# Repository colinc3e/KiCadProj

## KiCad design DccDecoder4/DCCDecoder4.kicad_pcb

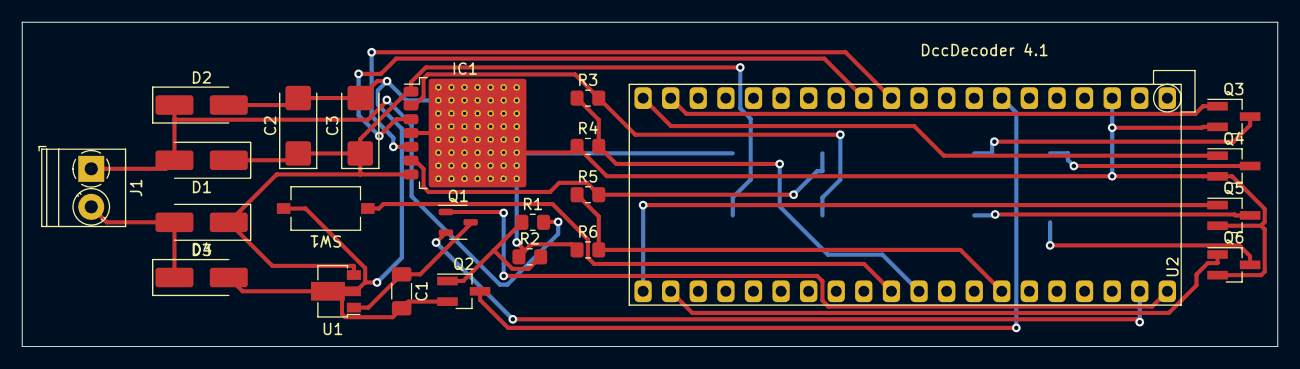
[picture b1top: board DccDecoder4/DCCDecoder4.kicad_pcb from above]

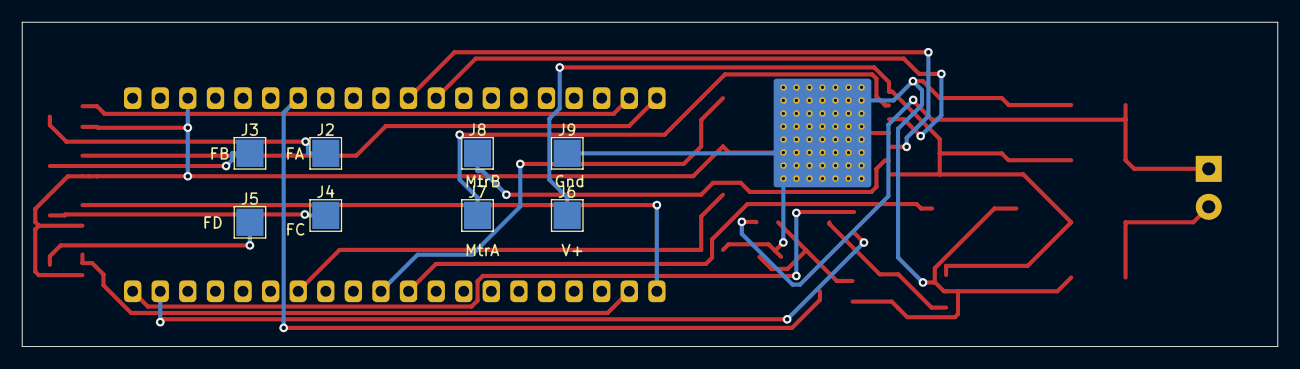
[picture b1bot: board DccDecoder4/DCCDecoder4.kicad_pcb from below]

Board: 2 copper layers, 115.6 x 29.8 mm, 32 parts (8 on the bottom side), 24 nets.

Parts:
C1: 10uf/16V; C_1206_3216Metric_Pad1.33x1.80mm_HandSolder
C2: 10uF/25V; CP_EIA-6032-20_AVX-F_Pad2.25x2.35mm_HandSolder
C3: 10uF/25v; CP_EIA-6032-20_AVX-F_Pad2.25x2.35mm_HandSolder
D1, D2, D3, D4: RBR3L60AD; D_SMA_Handsoldering
IC1: BD62321HFP-TR; Rohm_HRP7
J1: Screw_Terminal_01x02; TerminalBlock_Phoenix_PT-1,5-2-3.5-H_1x02_P3.50mm_Horizontal
J2: 0; TestPoint_Pad_2.5x2.5mm
J3: 1; TestPoint_Pad_2.5x2.5mm
J4: 2; TestPoint_Pad_2.5x2.5mm
J5: 3; TestPoint_Pad_2.5x2.5mm
J6: +V; TestPoint_Pad_2.5x2.5mm
J7: M_OUT_B; TestPoint_Pad_2.5x2.5mm
J8: M_OUT_A; TestPoint_Pad_2.5x2.5mm
J9: GND; TestPoint_Pad_2.5x2.5mm
Q1: DMG2305UX-7; SOT-23-3
Q2, Q3, Q4, Q5, Q6: 2N7002BK; SOT-23_Handsoldering
R1, R2, R3, R5: 6k8; R_0805_2012Metric_Pad1.20x1.40mm_HandSolder
R4, R6: 1k; R_0805_2012Metric_Pad1.20x1.40mm_HandSolder
SW1: SW_Push; SW_Tactile_SPST_NO_Straight_CK_PTS636Sx25SMTRLFS
U1: AP7384-50Y; SOT-89-3
U2: Pico_RaspberryPico; RaspberryPico_TH_NoSWD

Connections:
+V: C2.1, C3.1, D1.1 (K), D4.1 (K), IC1.1 (VCC_1), IC1.7 (VCC_2), J6.1, U1.3 (VI)
/+3V3: C1.1, Q1.3, U1.1 (VO)
/ADC_EMF_A: R3.1, R4.2, U2.31 (GPIO26)
/MOTOR_OUT_A: IC1.2 (OUT1), J7.1, R3.2
/MOTOR_OUT_B: IC1.6 (OUT2), J8.1, R5.2
/VSYS: Q1.2, U2.39 (VSYS)
ADC_EMF_B: R5.1, R6.2, U2.34 (GPIO28)
DCC_IN: Q2.3 (D), U2.7 (GPIO5)
FUNC_A: Q3.1 (G), U2.19 (GPIO14)
FUNC_B: Q4.1 (G), U2.20 (GPIO15)
FUNC_C: Q5.1 (G), U2.21 (GPIO16)
FUNC_D: Q6.1 (G), U2.22 (GPIO17)
GND: C1.2, C2.2, C3.2, D2.2 (A), D3.2 (A), IC1.4 (GND_1), J9.1, Q2.2 (S), Q3.2 (S), Q4.2 (S), Q5.2 (S), Q6.2 (S), R2.1, R4.1, R6.1, SW1.2, U1.2 (GND), U2.3 (GND)
unnamed: D1.2 (A), D2.1 (K), J1.1, R1.2
unnamed: D3.1 (K), D4.2 (A), J1.2
unnamed: J2.1, Q3.3 (D)
unnamed: J3.1, Q4.3 (D)
unnamed: J4.1, Q5.3 (D)
unnamed: J5.1, Q6.3 (D)
unnamed: Q2.1 (G), R1.1, R2.2
unnamed: SW1.1, U2.30 (RUN)
unnamed: Q1.1, U2.40 (VBUS)
PWM_F: IC1.3 (FIN), U2.12 (GPIO9)
PWM_R: IC1.5 (RIN), U2.11 (GPIO8)

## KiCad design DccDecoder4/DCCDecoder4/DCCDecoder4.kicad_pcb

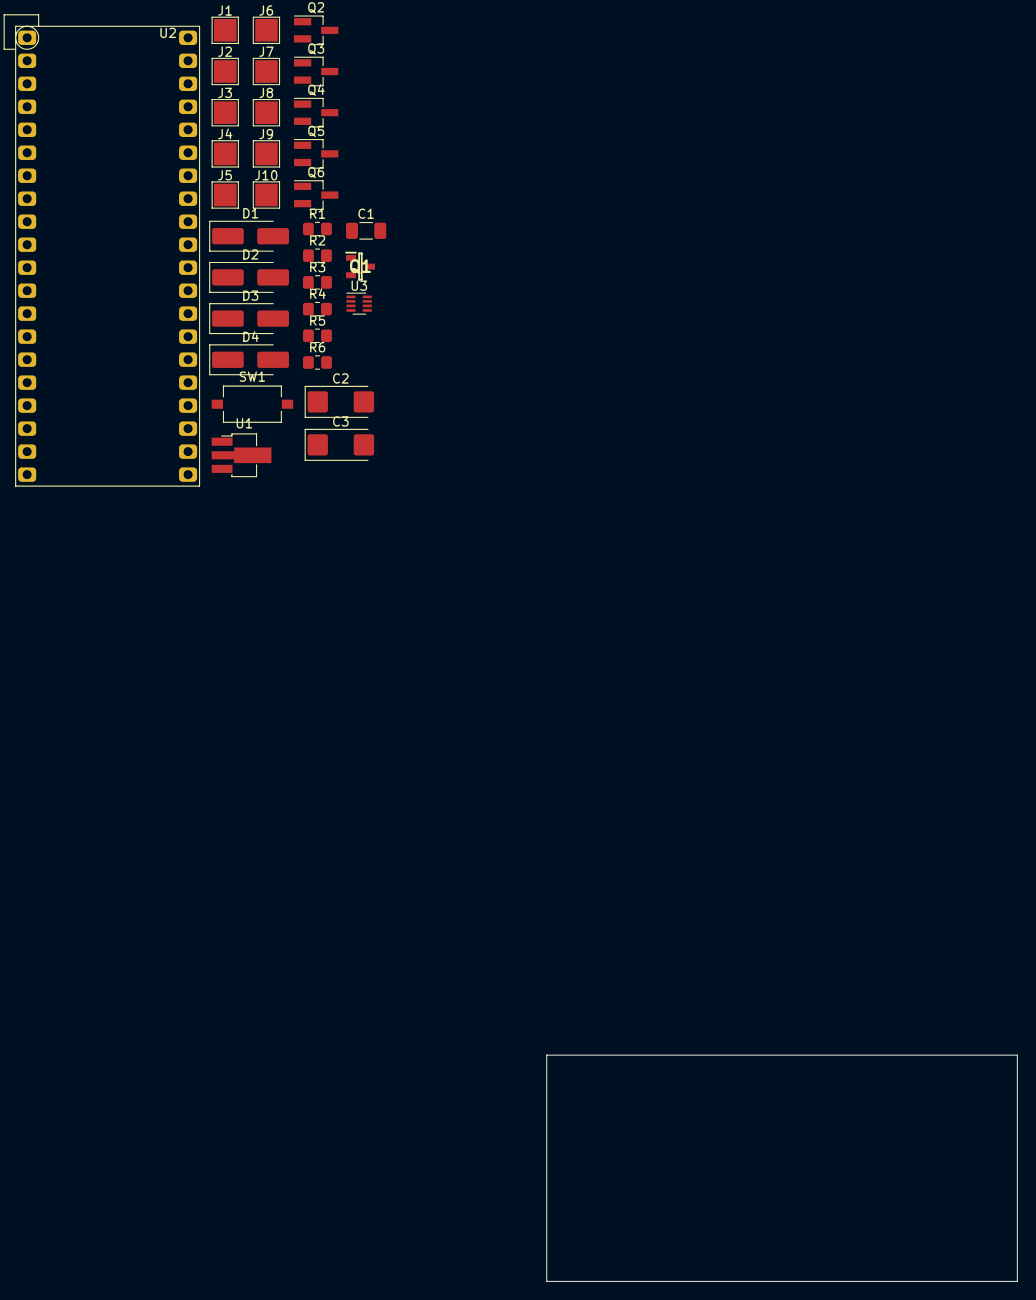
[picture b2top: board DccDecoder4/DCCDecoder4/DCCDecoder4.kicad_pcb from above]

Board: 2 copper layers, 52.0 x 25.0 mm, 33 parts (0 on the bottom side), 24 nets, no tracks yet.

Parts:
C1: 10uf/16V; C_1206_3216Metric_Pad1.33x1.80mm_HandSolder
C2: 10uF/25V; CP_EIA-6032-20_AVX-F_Pad2.25x2.35mm_HandSolder
C3: 10uF/25v; CP_EIA-6032-20_AVX-F_Pad2.25x2.35mm_HandSolder
D1, D2, D3, D4: RBR3L60AD; D_SMA_Handsoldering
J1, J2: PAD; TestPoint_Pad_2.5x2.5mm
J3: 0; TestPoint_Pad_2.5x2.5mm
J4: 1; TestPoint_Pad_2.5x2.5mm
J5: 2; TestPoint_Pad_2.5x2.5mm
J6: 3; TestPoint_Pad_2.5x2.5mm
J7: +V; TestPoint_Pad_2.5x2.5mm
J8: M_OUT_B; TestPoint_Pad_2.5x2.5mm
J9: M_OUT_A; TestPoint_Pad_2.5x2.5mm
J10: GND; TestPoint_Pad_2.5x2.5mm
Q1: DMG2305UX-7; SOT96P240X110-3N
Q2, Q3, Q4, Q5, Q6: 2N7002K; SOT-23_Handsoldering
R1, R2, R3, R5: 6k8; R_0805_2012Metric_Pad1.20x1.40mm_HandSolder
R4, R6: 1k; R_0805_2012Metric_Pad1.20x1.40mm_HandSolder
SW1: SW_Push; SW_Tactile_SPST_NO_Straight_CK_PTS636Sx25SMTRLFS
U1: AP7384-33Y; SOT-89-3_Handsoldering
U2: Pico_RaspberryPico; RaspberryPico_TH_NoSWD
U3: BDR6133; SC-70-8

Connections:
+3V3: C1.1, Q1.3, U1.1 (VO), U3.2 (VCC)
+V: C2.1, C3.1, D1.1 (K), D4.1 (K), J7.1, U1.3 (VI), U3.3 (VM)
/ADC_EMF_A: R3.1, R4.2, U2.31 (GPIO26)
/ADC_EMF_B: R5.1, R6.2, U2.32 (GPIO27)
/GPIO14: U2.19 (GPIO14), U3.6 (INA)
/GPIO15: U2.20 (GPIO15), U3.7 (INB)
/GPIO16: Q3.1 (G), U2.21 (GPIO16)
/GPIO17: Q4.1 (G), U2.22 (GPIO17)
/GPIO18: Q5.1 (G), U2.24 (GPIO18)
/GPIO19: Q6.1 (G), U2.25 (GPIO19)
/GPIO21: Q2.3 (D), U2.27 (GPIO21)
/MOTOR_OUT_A: J8.1, R3.2, U3.4 (OUTA)
/MOTOR_OUT_B: J9.1, R5.2, U3.5 (OUTB)
/VSYS: Q1.2, U2.39 (VSYS)
GND: C1.2, C2.2, C3.2, D2.2 (A), D3.2 (A), J10.1, Q2.2 (S), Q3.2 (S), Q4.2 (S), Q5.2 (S), Q6.2 (S), R2.1, R4.1, R6.1, SW1.2, U1.2 (GND), U2.3 (GND), U3.1 (GND)
unnamed: D1.2 (A), D2.1 (K), J1.1, R1.2
unnamed: D3.1 (K), D4.2 (A), J2.1
unnamed: J3.1, Q3.3 (D)
unnamed: J4.1, Q4.3 (D)
unnamed: J5.1, Q5.3 (D)
unnamed: J6.1, Q6.3 (D)
unnamed: Q2.1 (G), R1.1, R2.2
unnamed: SW1.1, U2.30 (RUN)
unnamed: Q1.1, U2.40 (VBUS)

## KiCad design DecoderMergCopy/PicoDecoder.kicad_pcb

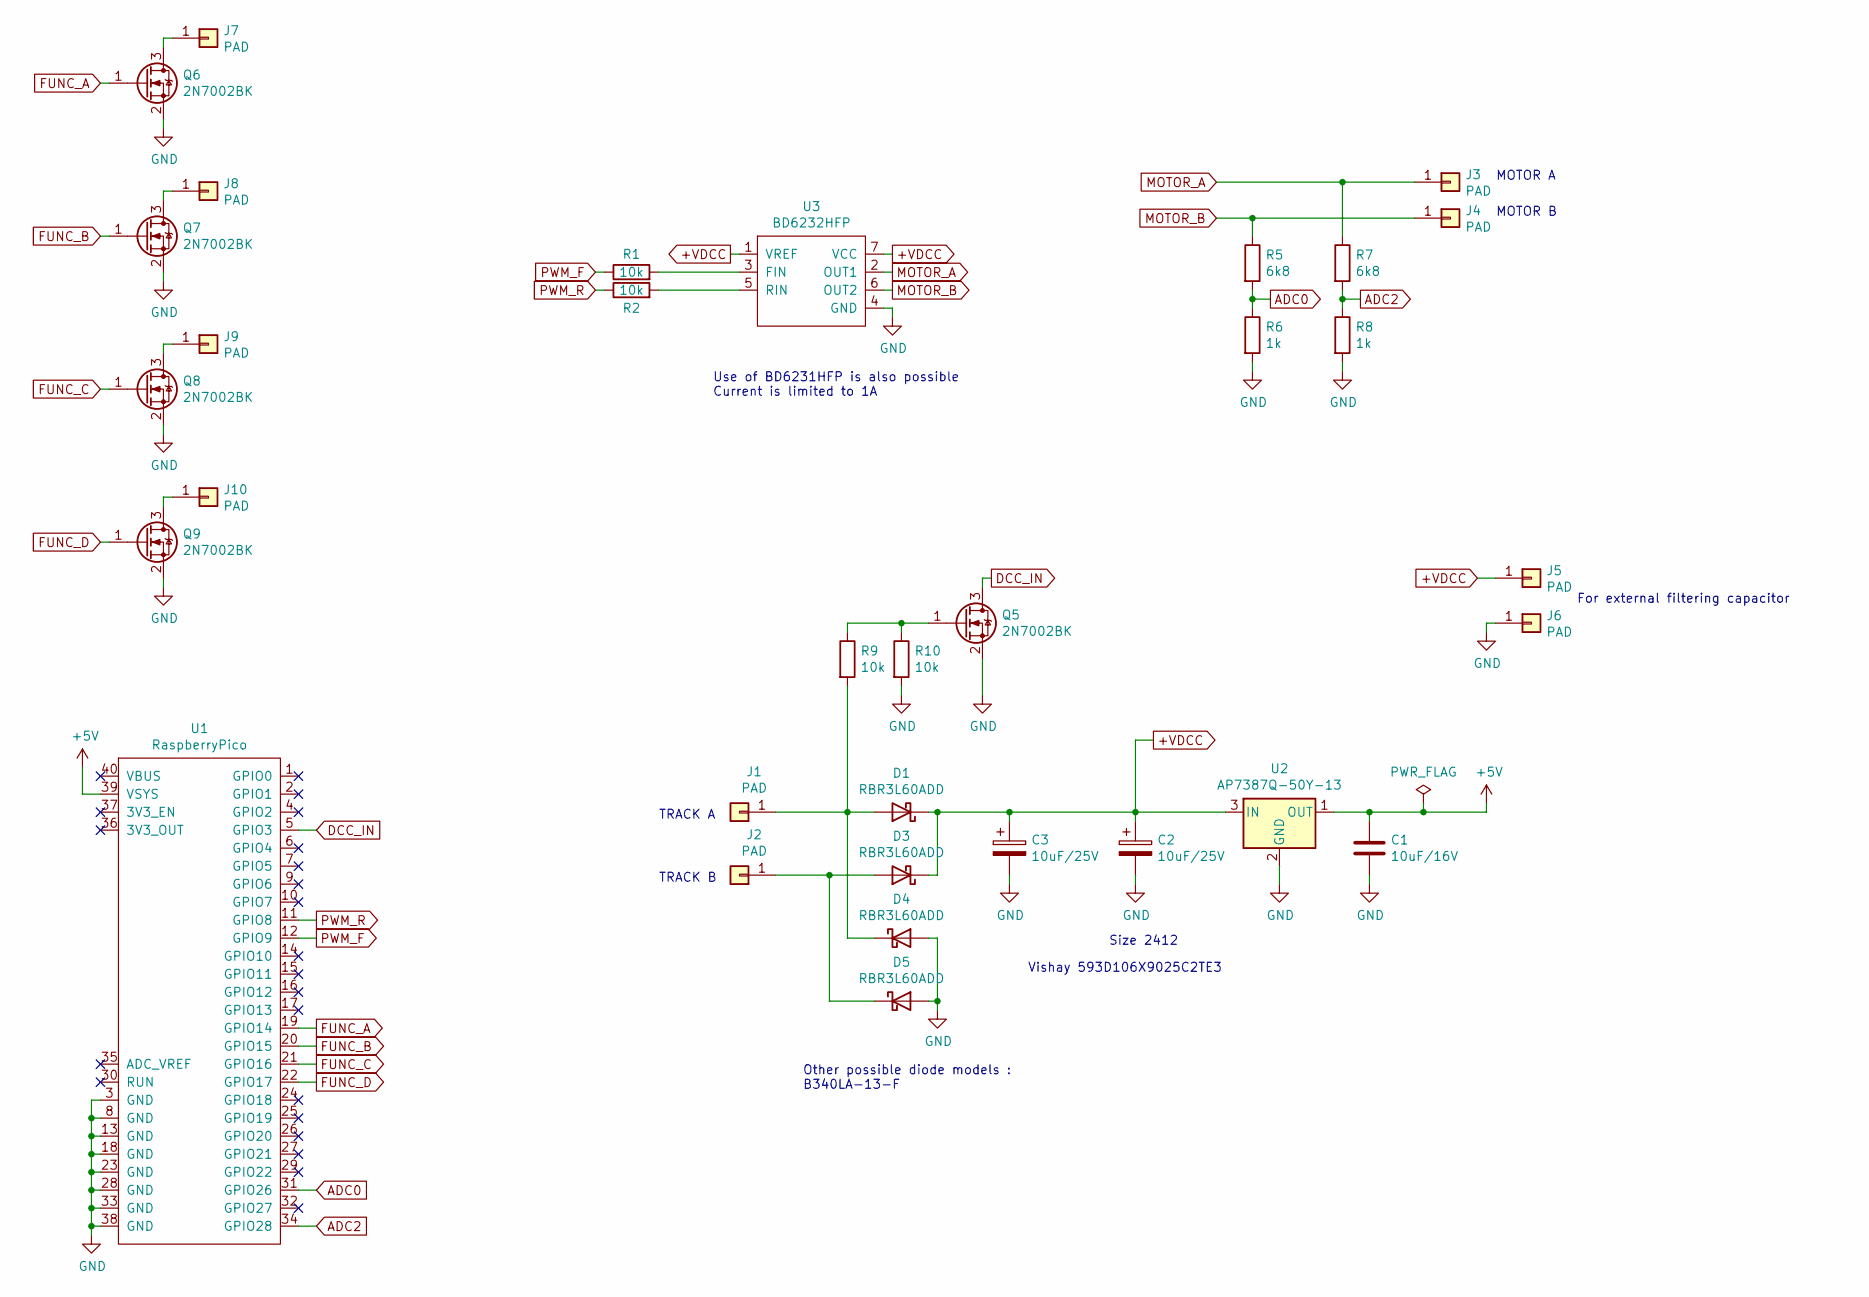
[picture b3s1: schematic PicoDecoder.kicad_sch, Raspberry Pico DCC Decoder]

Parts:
C1: 10uF/16V; C_1206_3216Metric_Pad1.33x1.80mm_HandSolder
C2, C3: 10uF/25V; CP_EIA-6032-20_AVX-F_Pad2.25x2.35mm_HandSolder
D1, D3, D4, D5: RBR3L60ADD; D_SMA_Handsoldering
J1, J2, J3, J4, J5, J6, J7, J8, J9, J10: PAD; TestPoint_Pad_2.5x2.5mm
Q5, Q6, Q7, Q8, Q9: 2N7002BK; SOT-23_Handsoldering
R1, R2, R9, R10: 10k; R_0805_2012Metric_Pad1.20x1.40mm_HandSolder
R5, R7: 6k8; R_0805_2012Metric_Pad1.20x1.40mm_HandSolder
R6, R8: 1k; R_0805_2012Metric_Pad1.20x1.40mm_HandSolder
U1: RaspberryPico; RaspberryPico_TH_NoSWD
U2: AP7387Q-50Y-13; SOT-89-3_Handsoldering
U3: BD6232HFP; Rohm_HRP7

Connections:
+5V: C1.1, U1.39 (VSYS), U2.1 (OUT)
+VDCC: C2.1, C3.1, D1.1 (K), D3.1 (K), J5.1, U2.3 (IN), U3.1 (VREF), U3.7 (VCC)
ADC0: R5.2, R6.1, U1.31 (GPIO26)
ADC2: R7.2, R8.1, U1.34 (GPIO28)
DCC_IN: Q5.3 (D), U1.5 (GPIO3)
FUNC_A: Q6.1 (G), U1.19 (GPIO14)
FUNC_B: Q7.1 (G), U1.20 (GPIO15)
FUNC_C: Q8.1 (G), U1.21 (GPIO16)
FUNC_D: Q9.1 (G), U1.22 (GPIO17)
GND: C1.2, C2.2, C3.2, D4.2 (A), D5.2 (A), J6.1, Q5.2 (S), Q6.2 (S), Q7.2 (S), Q8.2 (S), Q9.2 (S), R6.2, R8.2, R10.2, U1.3 (GND), U1.8 (GND), U1.13 (GND), U1.18 (GND), U1.23 (GND), U1.28 (GND), U1.33 (GND), U1.38 (GND), U2.2 (GND), U3.4 (GND)
MOTOR_A: J3.1, R7.1, U3.2 (OUT1)
MOTOR_B: J4.1, R5.1, U3.6 (OUT2)
unnamed: D1.2 (A), D4.1 (K), J1.1, R9.2
unnamed: D3.2 (A), D5.1 (K), J2.1
unnamed: J7.1, Q6.3 (D)
unnamed: J8.1, Q7.3 (D)
unnamed: J9.1, Q8.3 (D)
unnamed: J10.1, Q9.3 (D)
unnamed: Q5.1 (G), R9.1, R10.1
unnamed: R1.2, U3.3 (FIN)
unnamed: R2.2, U3.5 (RIN)
PWM_F: R1.1, U1.12 (GPIO9)
PWM_R: R2.1, U1.11 (GPIO8)

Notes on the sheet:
MOTOR A
Other possible diode models : B340LA-13-F
Size 2412
MOTOR B
TRACK B
Vishay 593D106X9025C2TE3
For external filtering capacitor
TRACK A
Use of BD6231HFP is also possible Current is limited to 1A

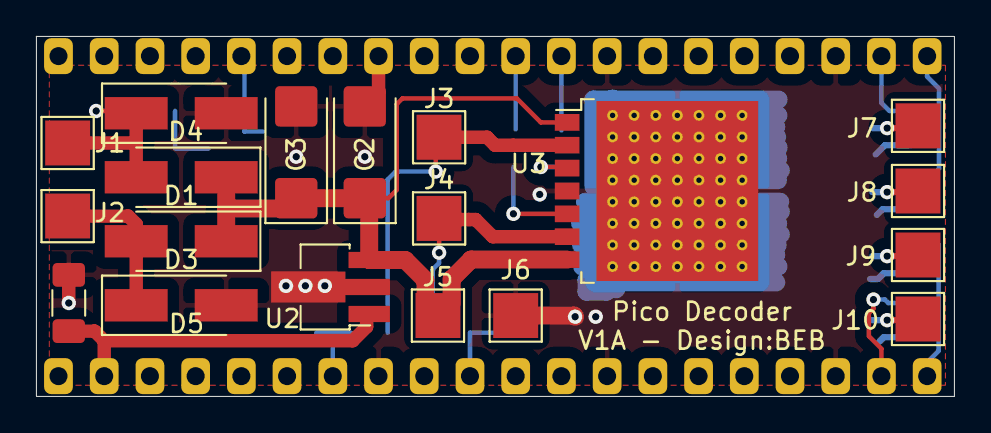
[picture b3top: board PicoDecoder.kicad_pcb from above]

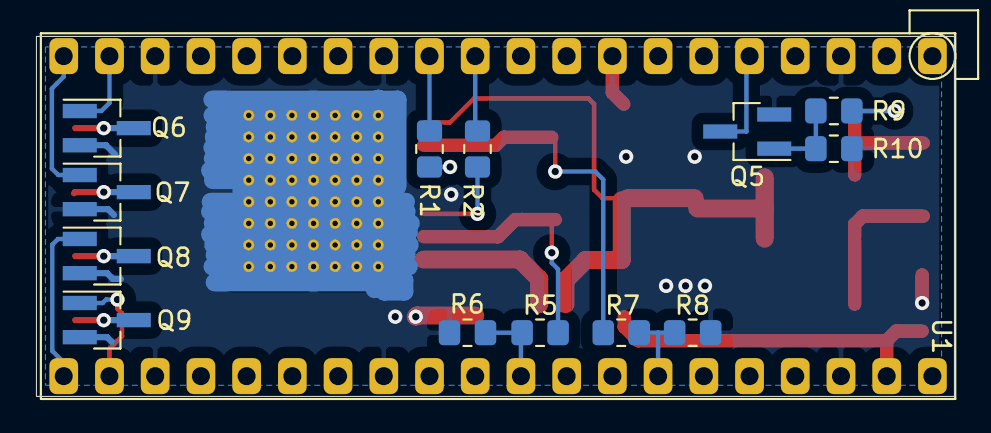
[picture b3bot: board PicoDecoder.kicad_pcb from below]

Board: 2 copper layers, 51.0 x 20.0 mm, 33 parts (14 on the bottom side), 23 nets.

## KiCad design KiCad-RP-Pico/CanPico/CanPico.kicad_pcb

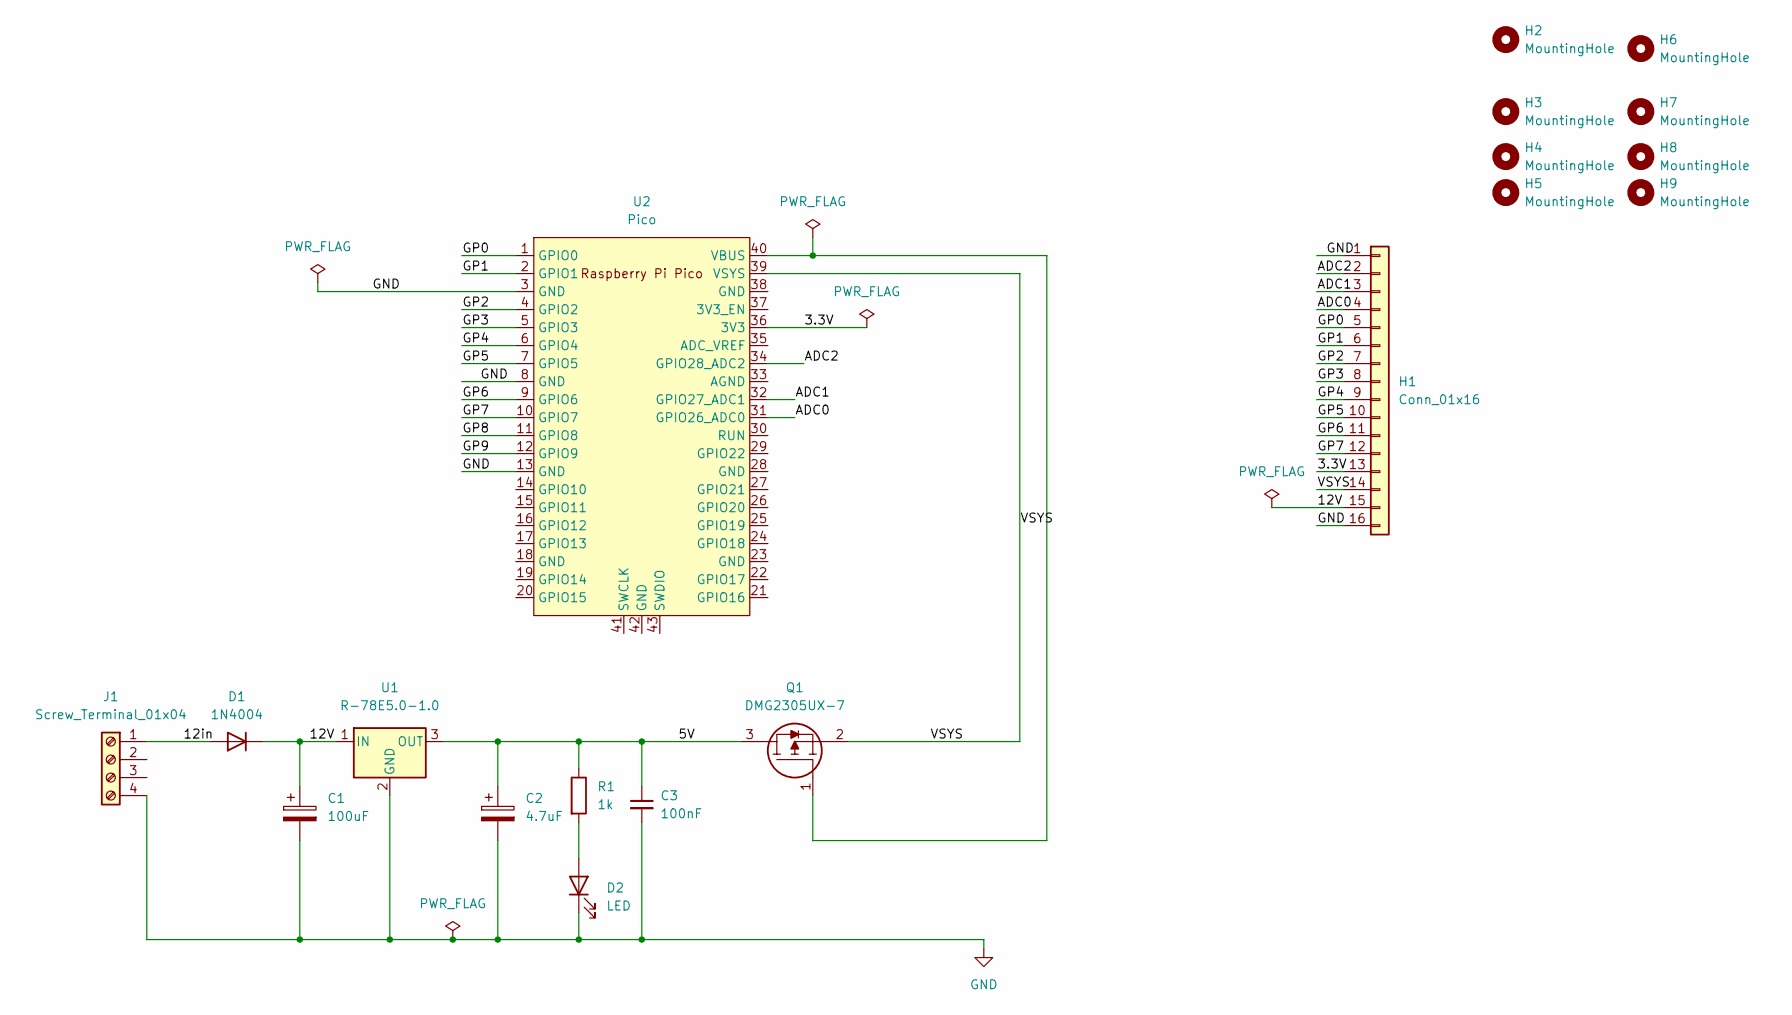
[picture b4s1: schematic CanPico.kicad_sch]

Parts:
C1: 100uF; CP_Radial_D6.3mm_P2.50mm
C2: 4.7uF; CP_Radial_D4.0mm_P1.50mm
C3: 100nF; C_Disc_D5.0mm_W2.5mm_P2.50mm
D1: 1N4004; D_DO-41_SOD81_P10.16mm_Horizontal
D2: LED; LED_D3.0mm
H1: Conn_01x16; PinHeader_1x16_P2.54mm_Vertical
H2, H3, H4, H5, H6, H7, H8, H9: MountingHole; MountingHole_3.2mm_M3
J1: Screw_Terminal_01x04; TerminalBlock_MetzConnect_Type059_RT06304HBWC_1x04_P3.50mm_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
Q1: DMG2305UX-7; SOT-23; Mouser Part Number 621-DMG2305UX-7
R1: 1k; R_Axial_DIN0207_L6.3mm_D2.5mm_P7.62mm_Horizontal
U1: R-78E5.0-1.0; Converter_DCDC_RECOM_R-78E-0.5_THT
U2: Pico; RPi_Pico_SMD_TH

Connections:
/3.3V: H1.13, U2.36 (3V3)
/5V: C2.1, C3.1, Q1.3, R1.1, U1.3 (OUT)
/12V: C1.1, D1.1 (K), H1.15, U1.1 (IN)
/12in: D1.2 (A), J1.1
/ADC0: H1.4, U2.31 (GPIO26_ADC0)
/ADC1: H1.3, U2.32 (GPIO27_ADC1)
/ADC2: H1.2, U2.34 (GPIO28_ADC2)
/GP0: H1.5, U2.1 (GPIO0)
/GP1: H1.6, U2.2 (GPIO1)
/GP2: H1.7, U2.4 (GPIO2)
/GP3: H1.8, U2.5 (GPIO3)
/GP4: H1.9, U2.6 (GPIO4)
/GP5: H1.10, U2.7 (GPIO5)
/GP6: H1.11, U2.9 (GPIO6)
/GP7: H1.12, U2.10 (GPIO7)
/GP8: U2.11 (GPIO8)
/GP9: U2.12 (GPIO9)
/VSYS: H1.14, Q1.2, U2.39 (VSYS)
GND: C1.2, C2.2, C3.2, D2.1 (K), H1.1, H1.16, J1.4, U1.2 (GND), U2.3 (GND), U2.8 (GND), U2.13 (GND)
unnamed: D2.2 (A), R1.2
unnamed: Q1.1, U2.40 (VBUS)

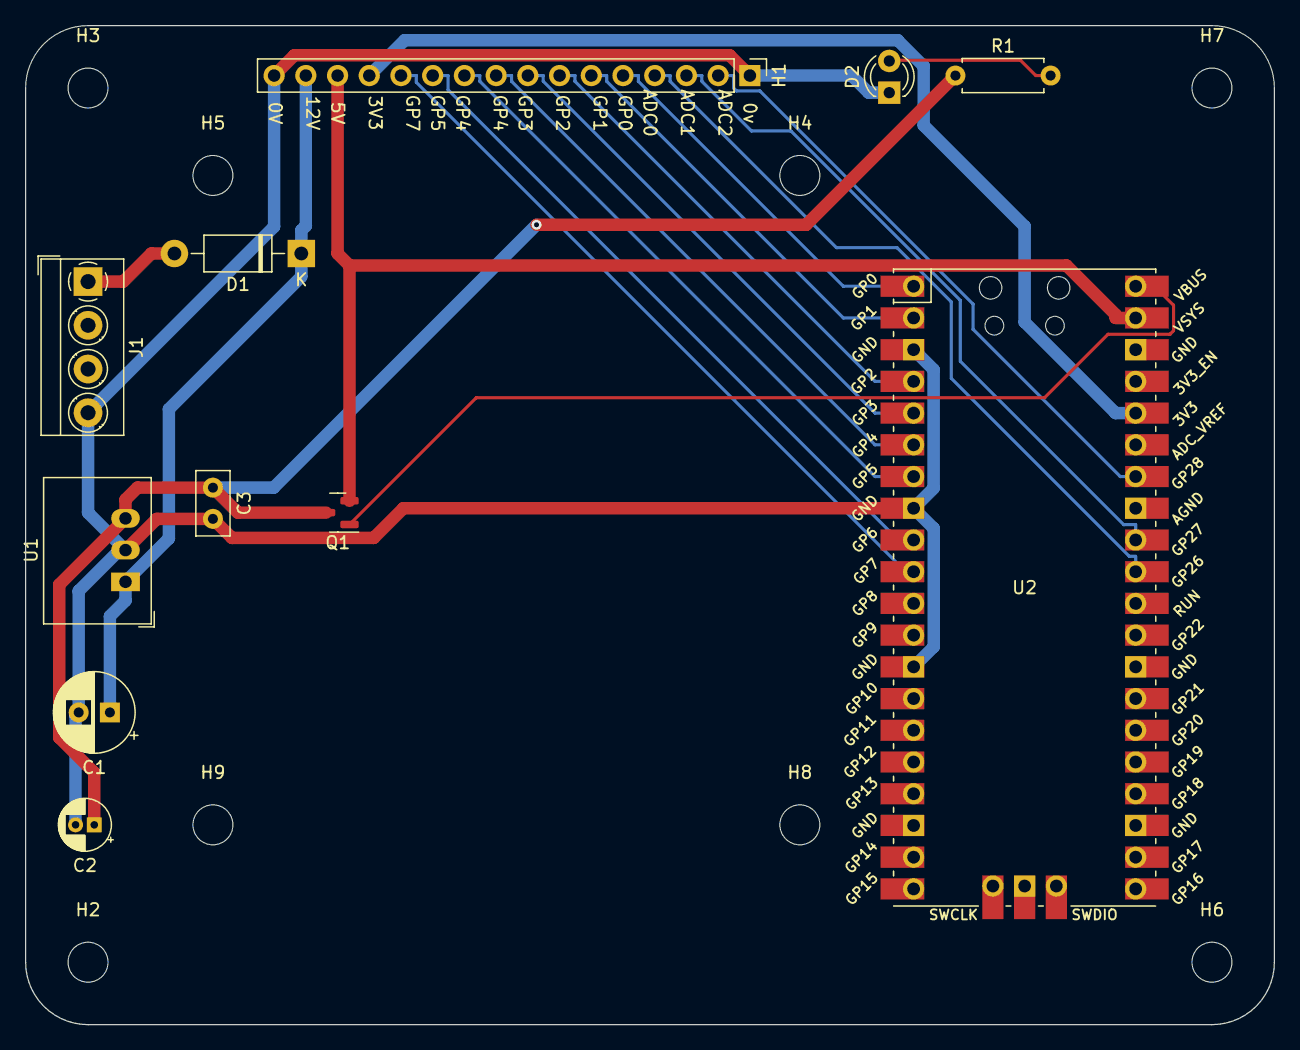
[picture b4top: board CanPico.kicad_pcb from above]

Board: 2 copper layers, 100.0 x 80.0 mm, 19 parts (0 on the bottom side), 19 nets.

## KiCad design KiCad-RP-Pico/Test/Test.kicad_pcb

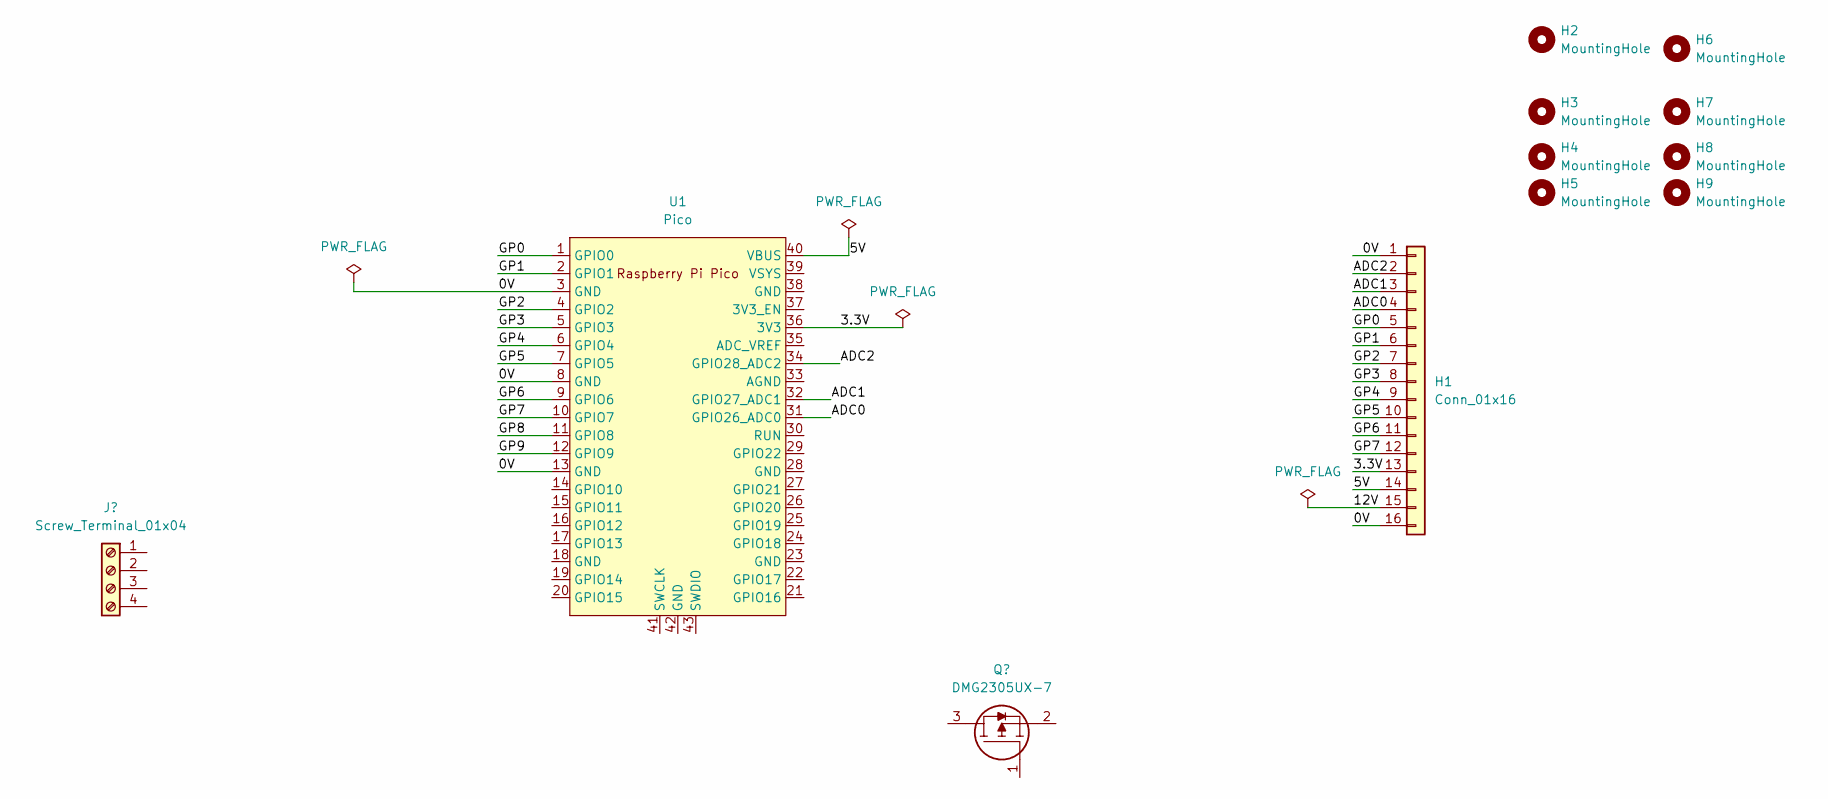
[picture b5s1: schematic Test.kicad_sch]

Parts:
H1: Conn_01x16; PinHeader_1x16_P2.54mm_Vertical
H2, H3, H4, H5, H6, H7, H8, H9: MountingHole; MountingHole_3.2mm_M3
U1: Pico; RPi_Pico_SMD_TH

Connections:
/0V: H1.1, H1.16, U1.3 (GND), U1.8 (GND), U1.13 (GND)
/3.3V: H1.13, U1.36 (3V3)
/5V: H1.14, U1.40 (VBUS)
/12V: H1.15
/ADC0: H1.4, U1.31 (GPIO26_ADC0)
/ADC1: H1.3, U1.32 (GPIO27_ADC1)
/ADC2: H1.2, U1.34 (GPIO28_ADC2)
/GP0: H1.5, U1.1 (GPIO0)
/GP1: H1.6, U1.2 (GPIO1)
/GP2: H1.7, U1.4 (GPIO2)
/GP3: H1.8, U1.5 (GPIO3)
/GP4: H1.9, U1.6 (GPIO4)
/GP5: H1.10, U1.7 (GPIO5)
/GP6: H1.11, U1.9 (GPIO6)
/GP7: H1.12, U1.10 (GPIO7)
/GP8: U1.11 (GPIO8)
/GP9: U1.12 (GPIO9)

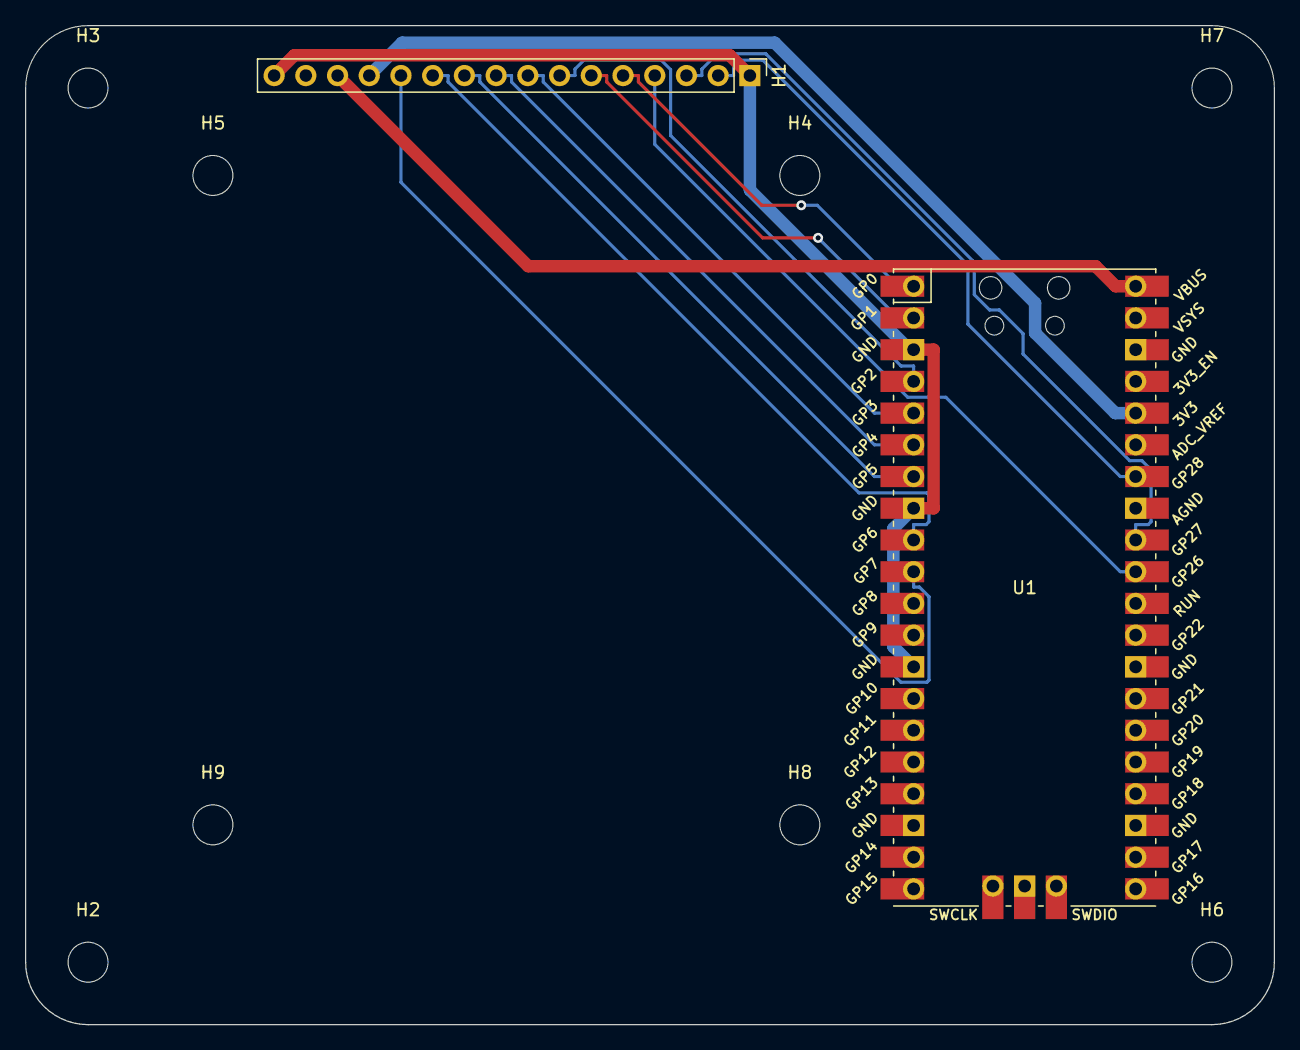
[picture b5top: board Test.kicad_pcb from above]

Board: 2 copper layers, 100.0 x 80.0 mm, 10 parts (0 on the bottom side), 14 nets.

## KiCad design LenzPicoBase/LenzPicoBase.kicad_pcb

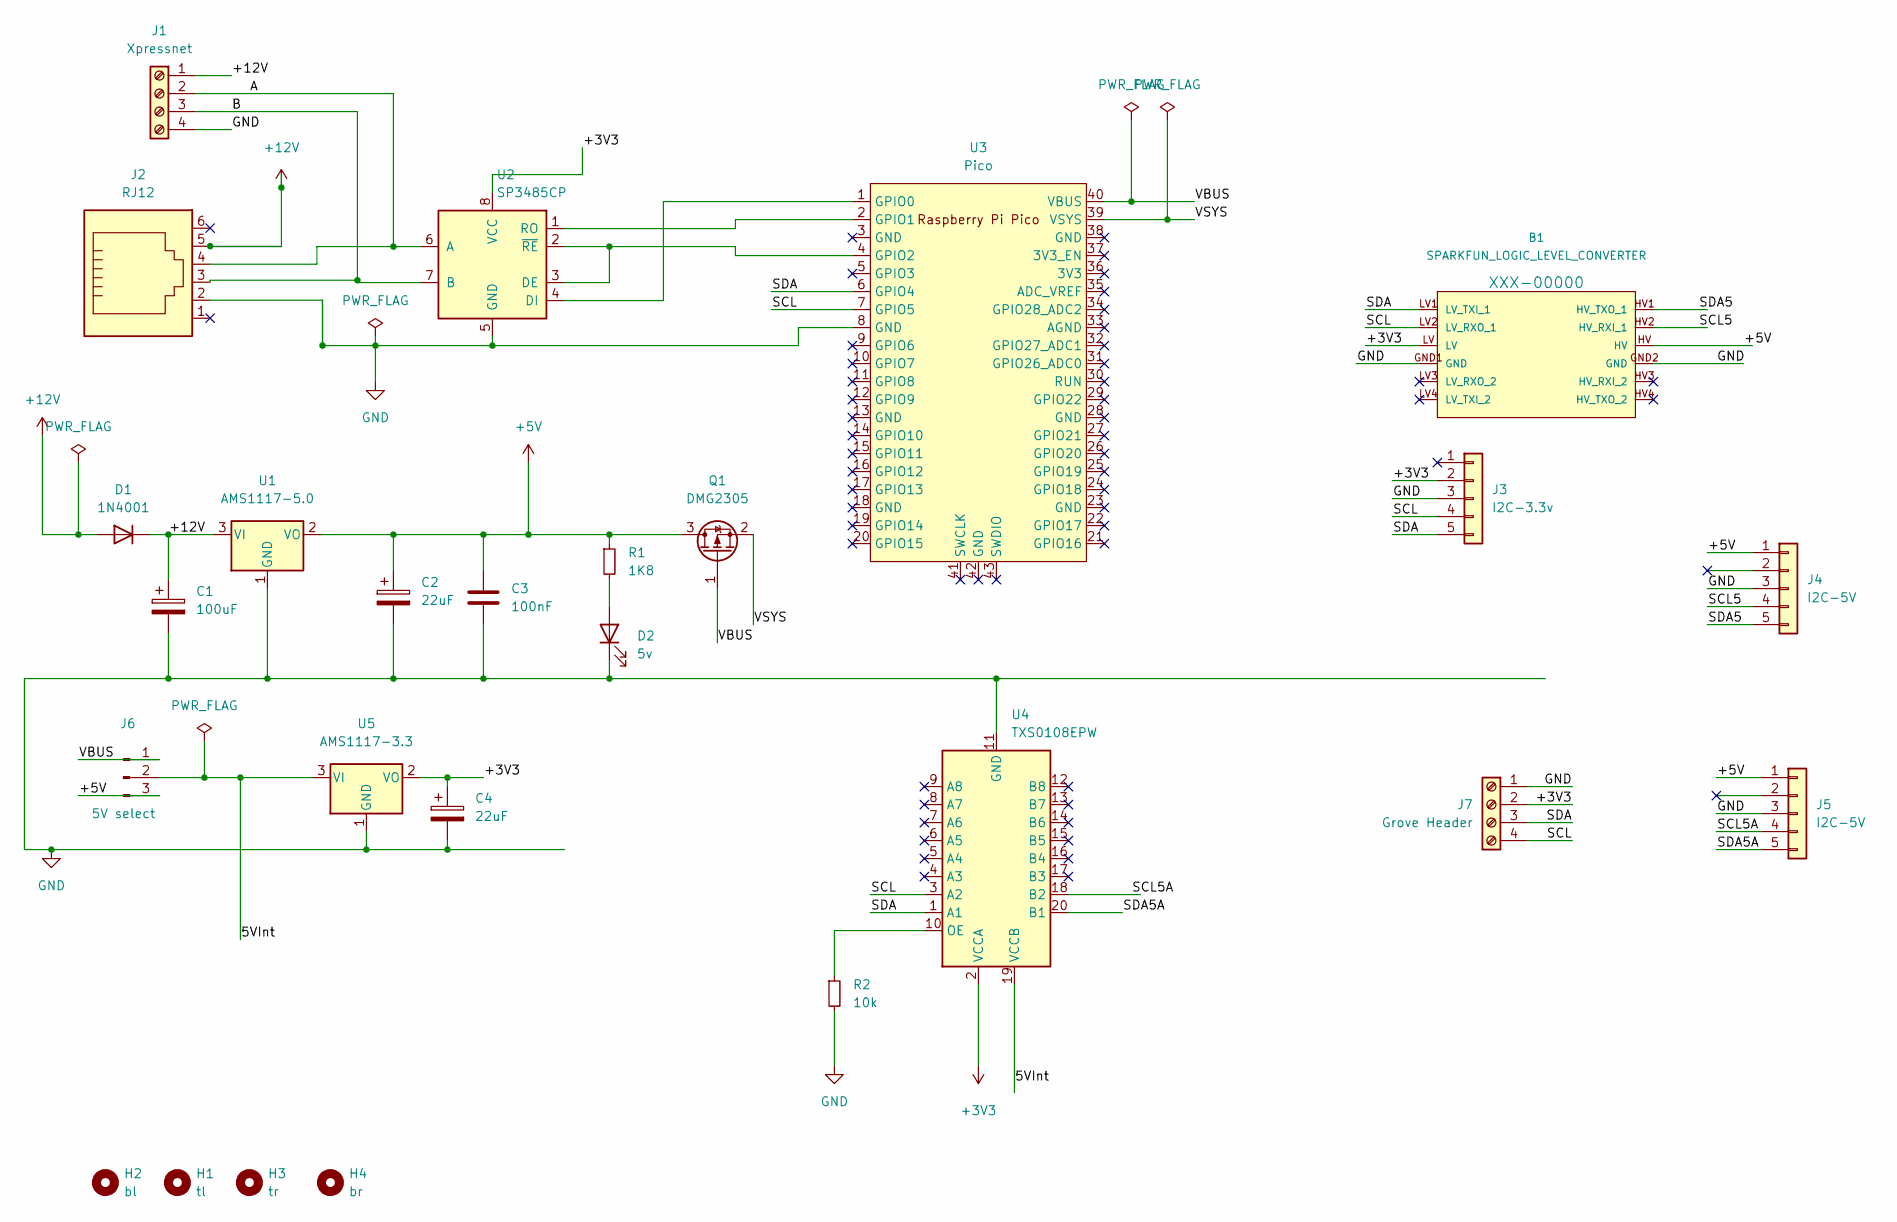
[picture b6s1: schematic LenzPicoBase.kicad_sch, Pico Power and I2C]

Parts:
B1: SPARKFUN_LOGIC_LEVEL_CONVERTER
C1: 100uF; CP_Radial_D8.0mm_P3.80mm
C2, C4: 22uF; CP_Radial_Tantal_D5.0mm_P5.00mm
C3: 100nF; C_Disc_D4.3mm_W1.9mm_P5.00mm
D1: 1N4001; D_DO-35_SOD27_P12.70mm_Horizontal
D2: 5v; LED_D3.0mm
H1: tl; MountingHole_3.2mm_M3_ISO7380
H2: bl; MountingHole_3.2mm_M3_ISO7380
H3: tr; MountingHole_3.2mm_M3_ISO7380
H4: br; MountingHole_3.2mm_M3_ISO7380
J1: Xpressnet; TerminalBlock_Phoenix_PT-1,5-4-3.5-H_1x04_P3.50mm_Horizontal
J2: RJ12; RJ12_Molex
J3: I2C-3.3v; PinHeader_1x05_P2.54mm_Vertical
J4, J5: I2C-5V; PinHeader_1x05_P2.54mm_Vertical
J6: 5V select; PinHeader_1x03_P2.54mm_Vertical
J7: Grove Header; Molex_KK-254_AE-6410-04A_1x04_P2.54mm_Vertical
Q1: DMG2305; SOT-23
R1: 1K8; R_Axial_DIN0207_L6.3mm_D2.5mm_P10.16mm_Horizontal
R2: 10k; R_Axial_DIN0207_L6.3mm_D2.5mm_P10.16mm_Horizontal
U1: AMS1117-5.0; SOT-223-3_TabPin2
U2: SP3485CP; DIP-8_W7.62mm
U3: Pico; RPi_Pico_SMD_TH
U4: TXS0108EPW; TSSOP-20_4.4x6.5mm_P0.65mm
U5: AMS1117-3.3; SOT-223-3_TabPin2

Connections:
+3V3: B1.LV, C4.1, J3.2, J7.2, U2.8 (VCC), U4.2 (VCCA), U5.2 (VO)
+5V: B1.HV, C2.1, C3.1, J4.1, J5.1, J6.3, Q1.3 (D), R1.1, U1.2 (VO)
+12V: C1.1, D1.1 (K), D1.2 (A), J1.1, J2.5, U1.3 (VI)
/5VInt: J6.2, U4.19 (VCCB), U5.3 (VI)
/A: J1.2, J2.4, U2.6 (A)
/B: J1.3, J2.3, U2.7 (B)
/SCL: B1.LV2 (LV_RXO_1), J3.4, J7.4, U3.7 (GPIO5), U4.3 (A2)
/SCL5: B1.HV2 (HV_RXI_1), J4.4
/SCL5A: J5.4, U4.18 (B2)
/SDA: B1.LV1 (LV_TXI_1), J3.5, J7.3, U3.6 (GPIO4), U4.1 (A1)
/SDA5: B1.HV1 (HV_TXO_1), J4.5
/SDA5A: J5.5, U4.20 (B1)
/VBUS: J6.1, Q1.1 (G), U3.40 (VBUS)
/VSYS: Q1.2 (S), U3.39 (VSYS)
GND: B1.GND1 (GND), B1.GND2 (GND), C1.2, C2.2, C3.2, C4.2, D2.1 (K), J1.4, J2.2, J3.3, J4.3, J5.3, J7.1, R2.2, U1.1 (GND), U2.5 (GND), U3.8 (GND), U4.11 (GND), U5.1 (GND)
unnamed: D2.2 (A), R1.2
unnamed: R2.1, U4.10 (OE)
unnamed: U2.1 (RO), U3.2 (GPIO1)
unnamed: U2.2 (~RE), U2.3 (DE), U3.4 (GPIO2)
unnamed: U2.4 (DI), U3.1 (GPIO0)

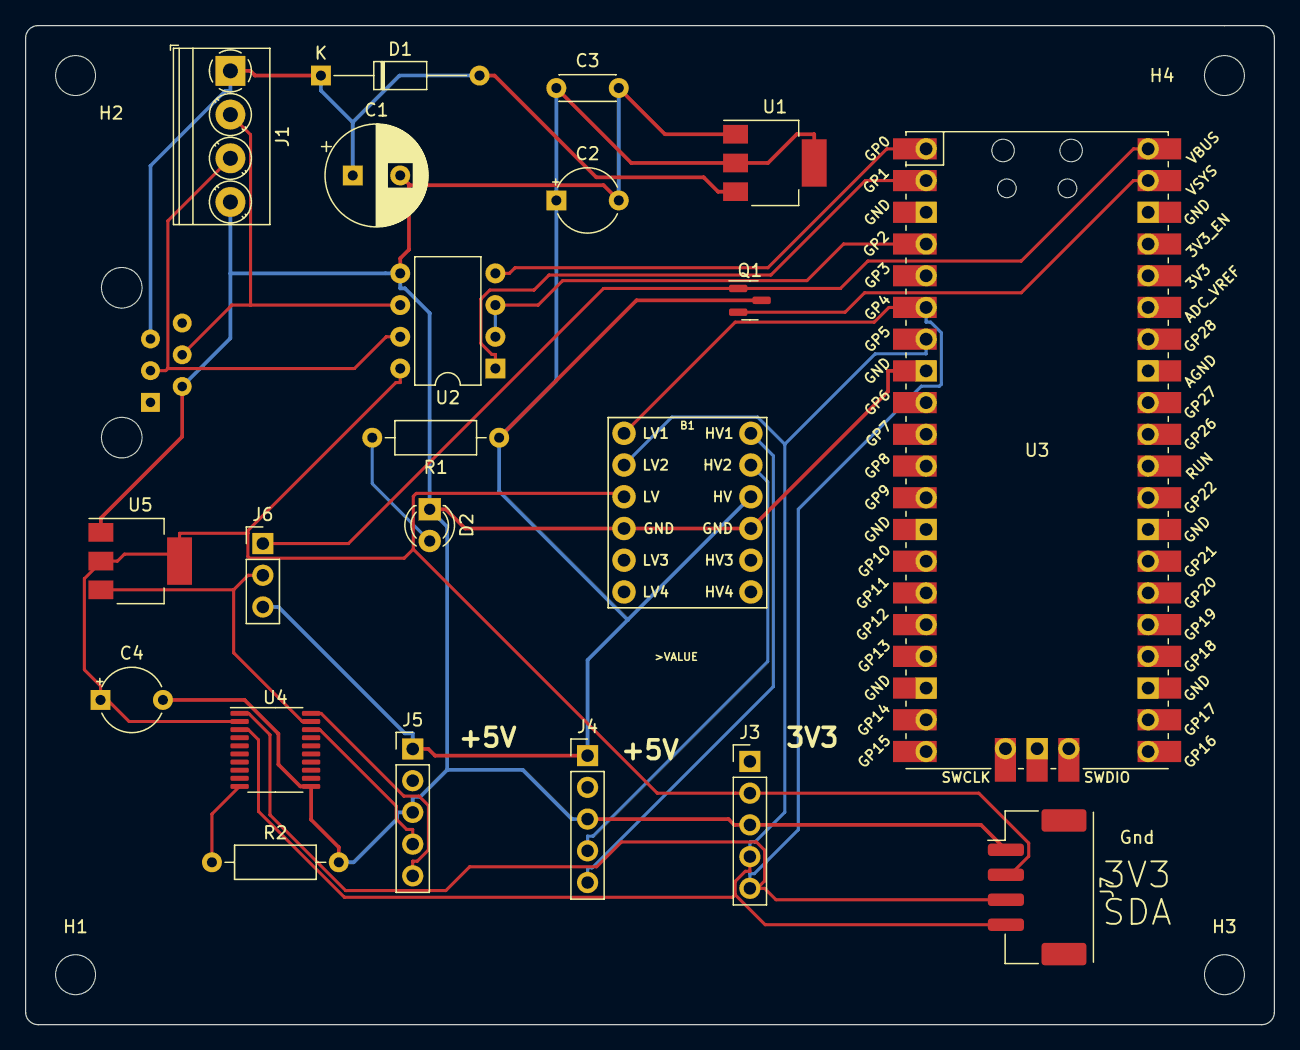
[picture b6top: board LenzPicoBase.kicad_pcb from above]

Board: 2 copper layers, 100.0 x 80.0 mm, 26 parts (1 on the bottom side), 20 nets.
